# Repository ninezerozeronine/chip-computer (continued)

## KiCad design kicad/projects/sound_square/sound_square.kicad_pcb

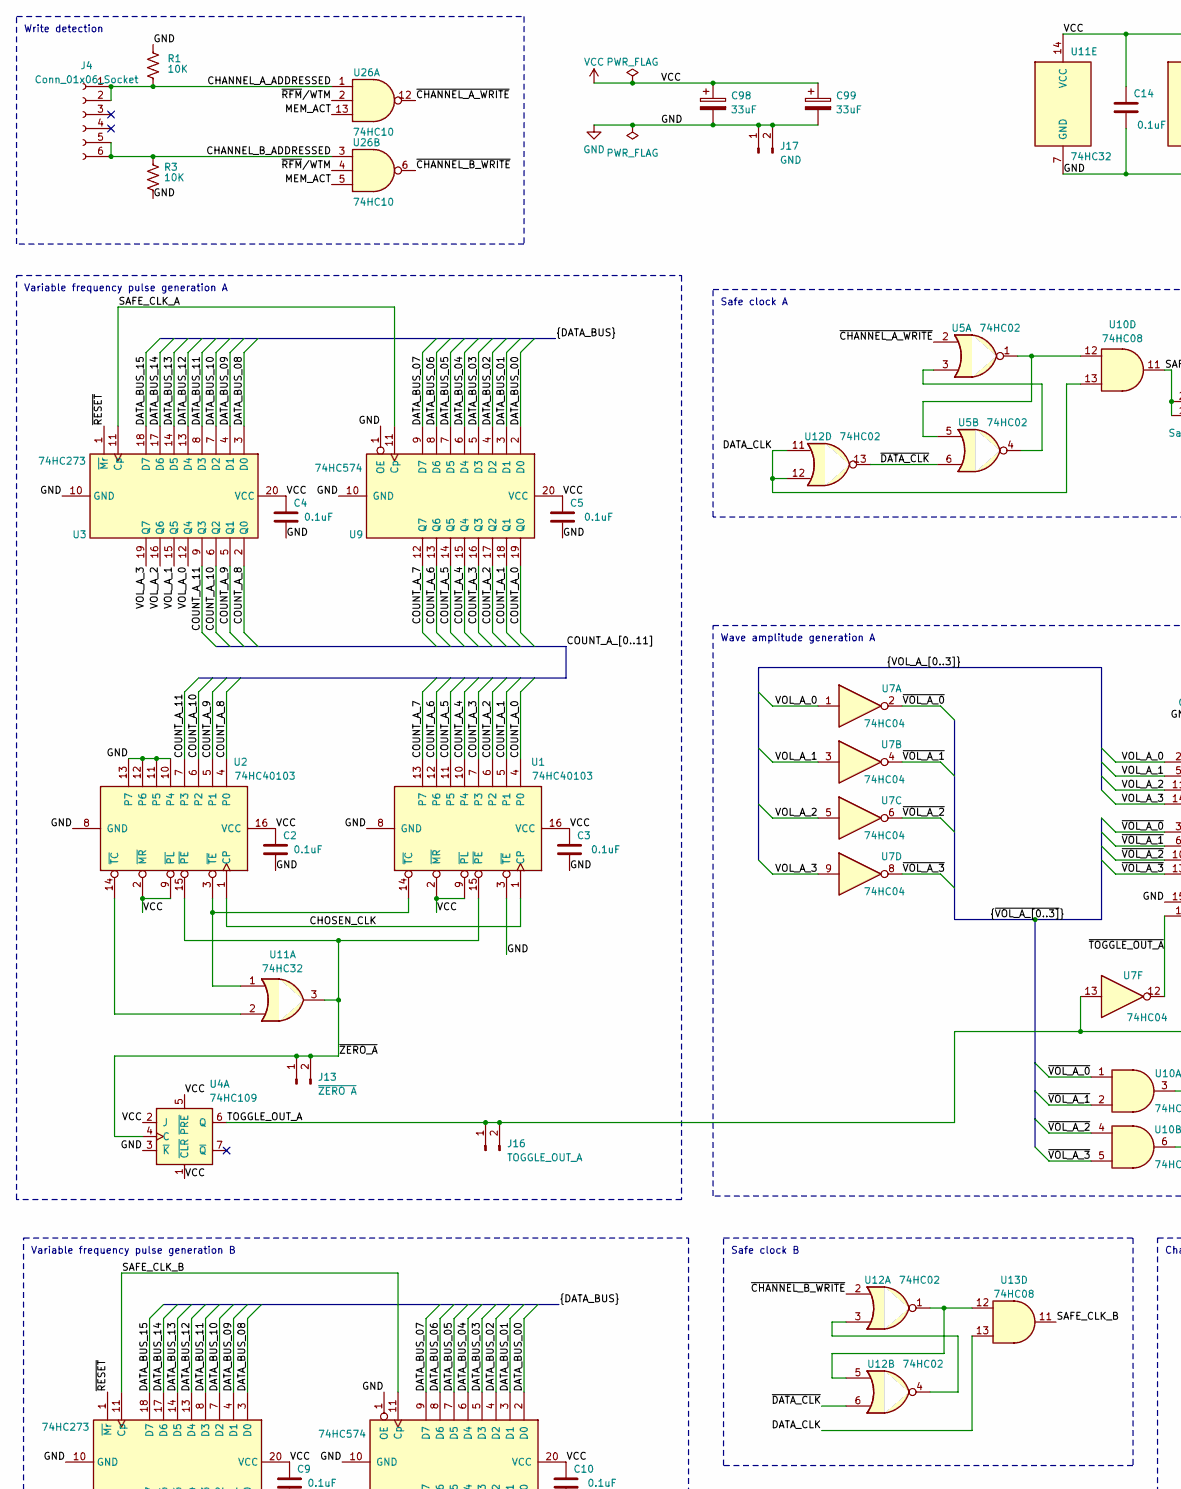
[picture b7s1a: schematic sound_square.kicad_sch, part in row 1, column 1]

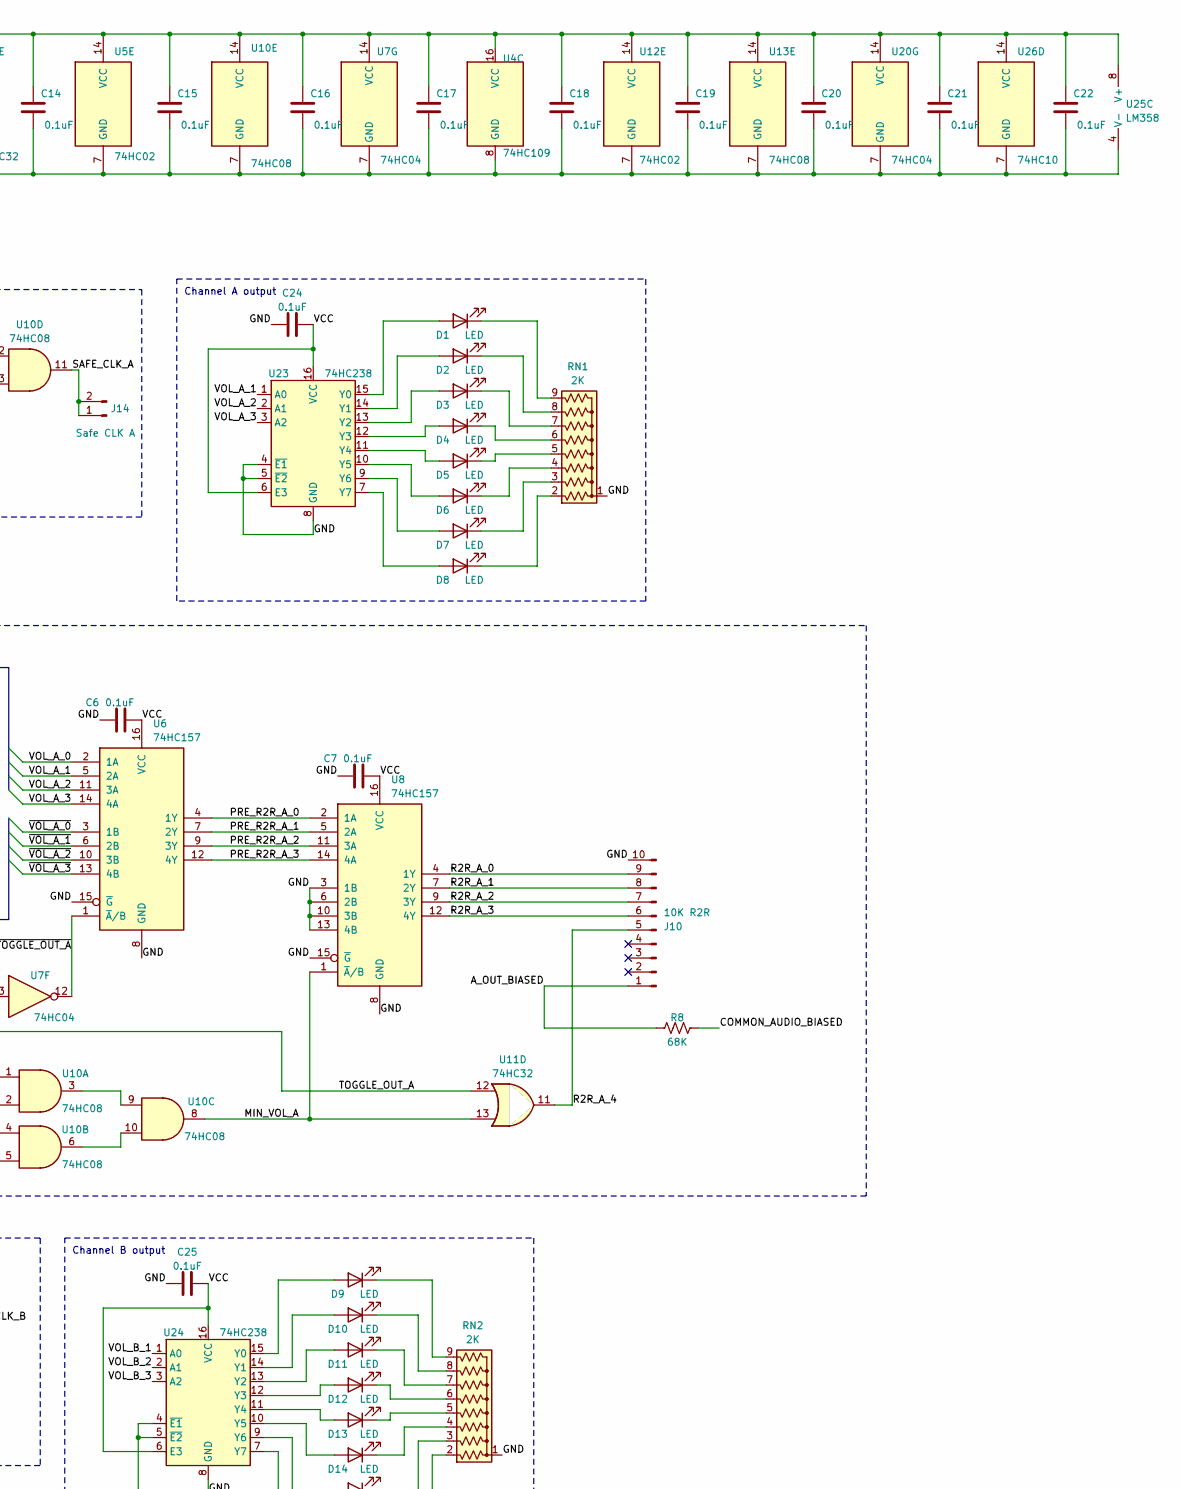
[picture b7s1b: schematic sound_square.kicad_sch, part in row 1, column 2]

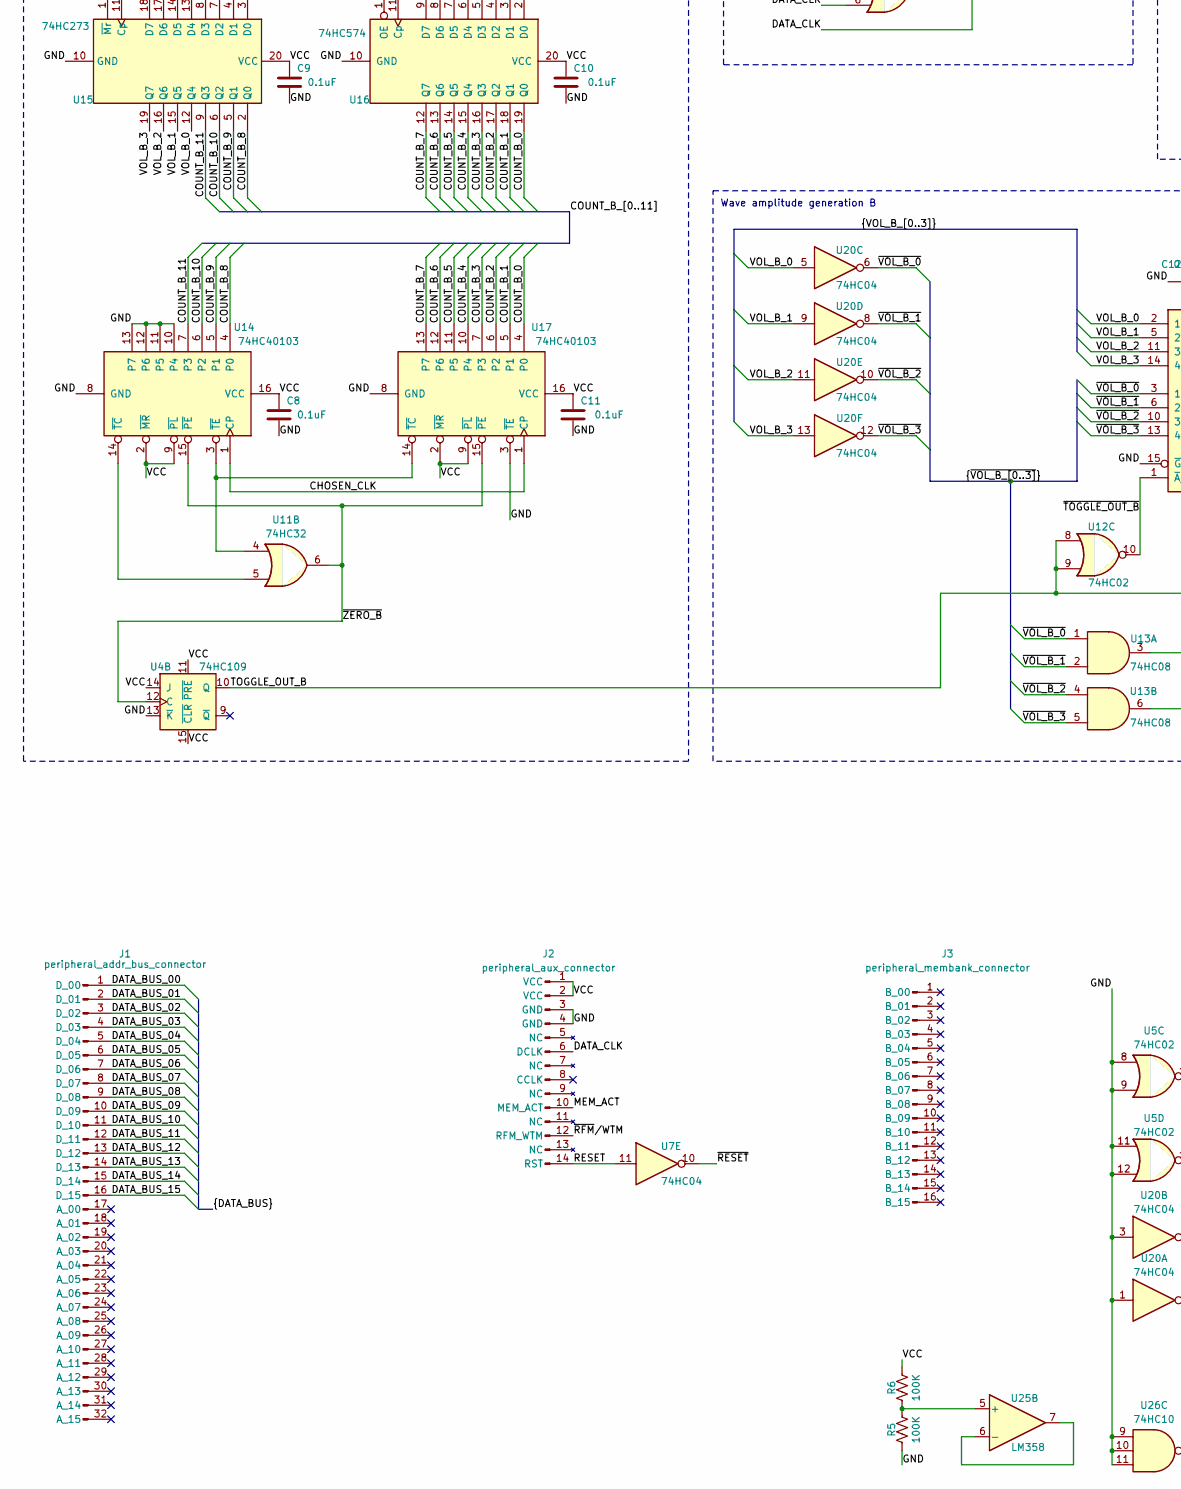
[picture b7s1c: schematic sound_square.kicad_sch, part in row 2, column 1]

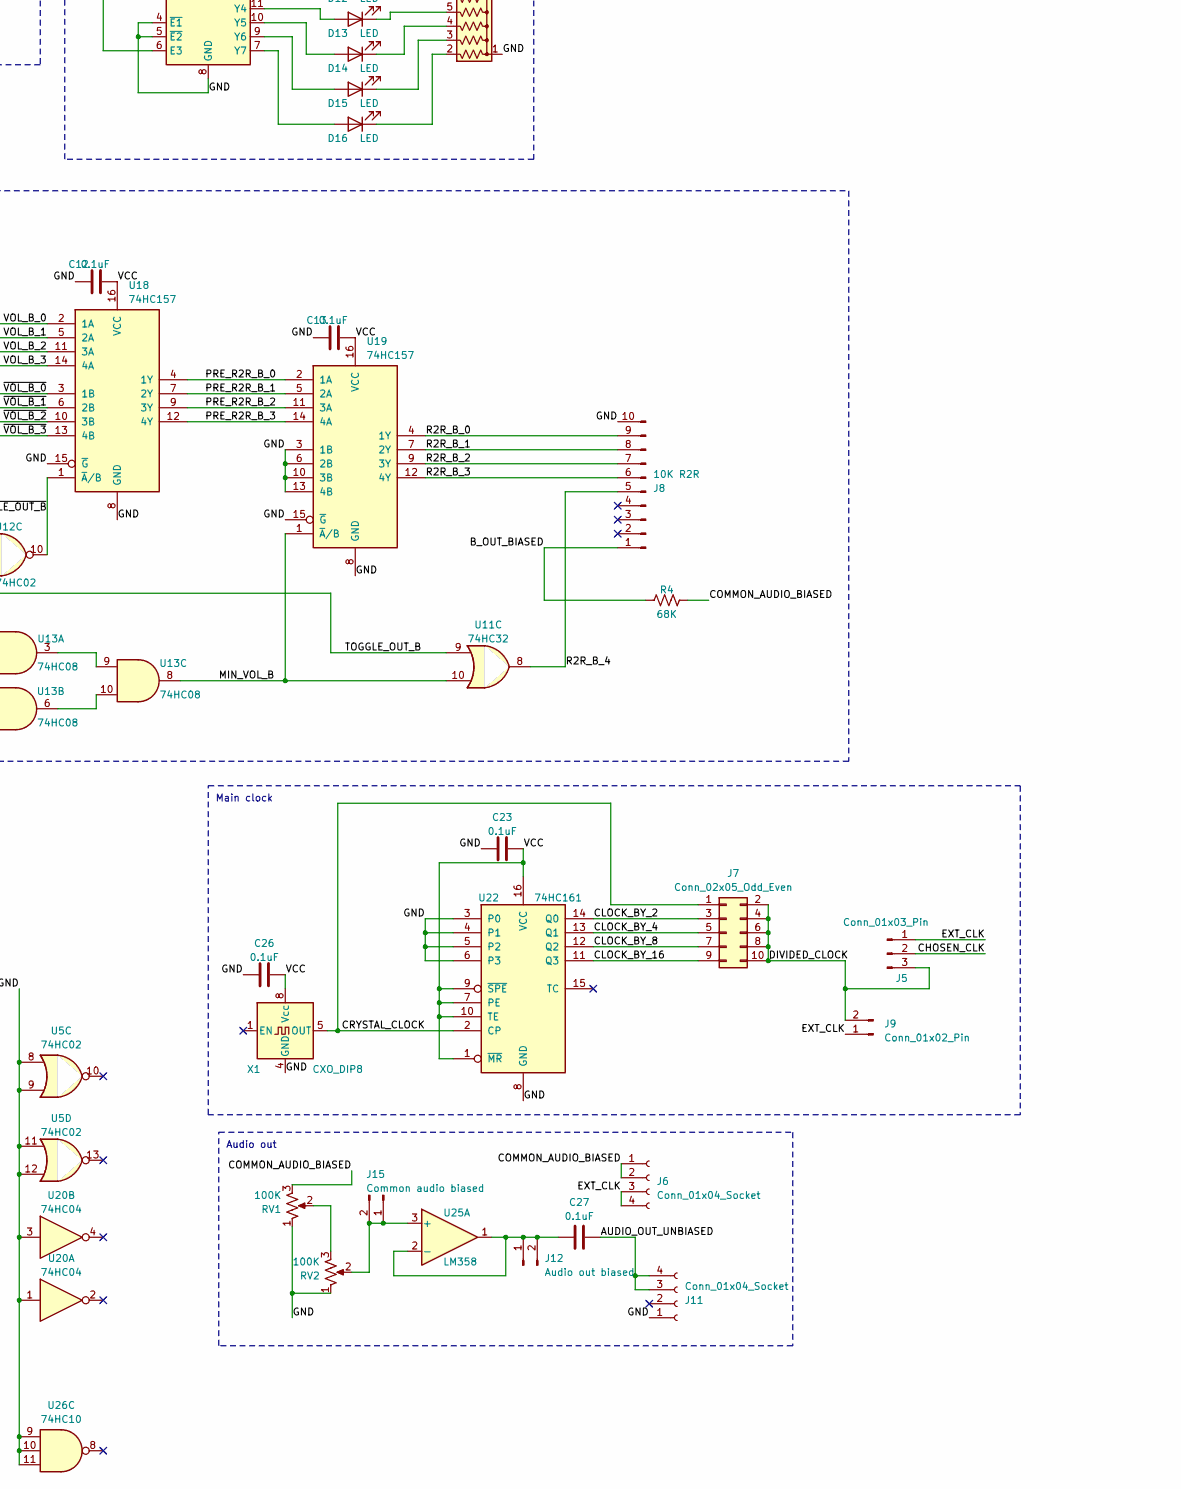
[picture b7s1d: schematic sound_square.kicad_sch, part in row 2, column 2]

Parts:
C2, C3, C4, C5, C6, C7, C8, C9, C10, C11, C12, C13, C14, C15, C16, C17, C18, C19, C20, C21, C22, C23, C24, C25, C26, C27: 0.1uF; C_Disc_D5.0mm_W2.5mm_P5.00mm
C98, C99: 33uF; CP_Radial_D6.3mm_P2.50mm
D1, D2, D3, D4, D5, D6, D7, D8, D9, D10, D11, D12, D13, D14, D15, D16: LED; LED_D5.0mm_Horizontal_O3.81mm_Z3.0mm
J1: peripheral_addr_bus_connector; peripheral-backplane-data-addr-anno
J2: peripheral_aux_connector; peripheral-backplane-aux
J3: peripheral_membank_connector; peripheral-backplane-membank
J4: Conn_01x06_Socket; PinSocket_1x06_P2.54mm_Horizontal
J5: Conn_01x03_Pin; PinHeader_1x03_P2.54mm_Vertical
J6, J11: Conn_01x04_Socket; PinSocket_1x04_P2.54mm_Horizontal
J7: Conn_02x05_Odd_Even; PinHeader_2x05_P2.54mm_Vertical
J8, J10: 10K R2R; R_Array_SIP10
J9: Conn_01x02_Pin; PinHeader_1x02_P2.54mm_Vertical
J12: Audio out biased; PinHeader_1x02_P2.54mm_Vertical
J13: ~{ZERO A}; PinHeader_1x02_P2.54mm_Vertical
J14: Safe CLK A; PinHeader_1x02_P2.54mm_Vertical
J15: Common audio biased; PinHeader_1x02_P2.54mm_Vertical
J16: TOGGLE_OUT_A; PinHeader_1x02_P2.54mm_Vertical
J17: GND; PinHeader_1x02_P2.54mm_Vertical
R1, R3: 10K; R_Axial_DIN0207_L6.3mm_D2.5mm_P10.16mm_Horizontal
R4, R8: 68K; R_Axial_DIN0207_L6.3mm_D2.5mm_P10.16mm_Horizontal
R5, R6: 100K; R_Axial_DIN0207_L6.3mm_D2.5mm_P10.16mm_Horizontal
RN1, RN2: 2K; R_Array_SIP9
RV1, RV2: 100K; Potentiometer_Bourns_3386P_Vertical
U1, U2, U14, U17: 74HC40103; DIP-16_W7.62mm_Socket
U3, U15: 74HC273; DIP-20_W7.62mm_Socket
U4: 74HC109; DIP-16_W7.62mm_Socket
U5, U12: 74HC02; DIP-14_W7.62mm_Socket
U6, U8, U18, U19: 74HC157; DIP-16_W7.62mm_Socket
U7, U20: 74HC04; DIP-14_W7.62mm_Socket
U9, U16: 74HC574; DIP-20_W7.62mm_Socket
U10, U13: 74HC08; DIP-14_W7.62mm_Socket
U11: 74HC32; DIP-14_W7.62mm_Socket
U22: 74HC161; DIP-16_W7.62mm_Socket
U23, U24: 74HC238; DIP-16_W7.62mm_Socket
U25: LM358; DIP-8_W7.62mm_Socket
U26: 74HC10; DIP-14_W7.62mm_Socket
X1: CXO_DIP8; Oscillator_DIP-8

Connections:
/AUDIO_OUT_UNBIASED: C27.2, J11.3, J11.4
/A_OUT_BIASED: J10.1, R8.1
/B_OUT_BIASED: J8.1, R4.1
/CHANNEL_A_ADDRESSED: J4.1, J4.2, R1.2, U26.1
/CHANNEL_B_ADDRESSED: J4.5, J4.6, R3.1, U26.3
/CHOSEN_CLK: J5.2, U1.1 (CP), U2.1 (CP), U14.1 (CP), U17.1 (CP)
/CLOCK_BY_2: J7.3, U22.14 (Q0)
/CLOCK_BY_4: J7.5, U22.13 (Q1)
/CLOCK_BY_8: J7.7, U22.12 (Q2)
/CLOCK_BY_16: J7.9, U22.11 (Q3)
/COMMON_AUDIO_BIASED: J6.1, J6.2, R4.2, R8.2, RV1.3
/COUNT_A_0: U1.4 (P0), U9.19 (Q0)
/COUNT_A_1: U1.5 (P1), U9.18 (Q1)
/COUNT_A_2: U1.6 (P2), U9.17 (Q2)
/COUNT_A_3: U1.7 (P3), U9.16 (Q3)
/COUNT_A_4: U1.10 (P4), U9.15 (Q4)
/COUNT_A_5: U1.11 (P5), U9.14 (Q5)
/COUNT_A_6: U1.12 (P6), U9.13 (Q6)
/COUNT_A_7: U1.13 (P7), U9.12 (Q7)
/COUNT_A_8: U2.4 (P0), U3.2 (Q0)
/COUNT_A_9: U2.5 (P1), U3.5 (Q1)
/COUNT_A_10: U2.6 (P2), U3.6 (Q2)
/COUNT_A_11: U2.7 (P3), U3.9 (Q3)
/COUNT_B_0: U16.19 (Q0), U17.4 (P0)
/COUNT_B_1: U16.18 (Q1), U17.5 (P1)
/COUNT_B_2: U16.17 (Q2), U17.6 (P2)
/COUNT_B_3: U16.16 (Q3), U17.7 (P3)
/COUNT_B_4: U16.15 (Q4), U17.10 (P4)
/COUNT_B_5: U16.14 (Q5), U17.11 (P5)
/COUNT_B_6: U16.13 (Q6), U17.12 (P6)
/COUNT_B_7: U16.12 (Q7), U17.13 (P7)
/COUNT_B_8: U14.4 (P0), U15.2 (Q0)
/COUNT_B_9: U14.5 (P1), U15.5 (Q1)
/COUNT_B_10: U14.6 (P2), U15.6 (Q2)
/COUNT_B_11: U14.7 (P3), U15.9 (Q3)
/CRYSTAL_CLOCK: J7.1, U22.2 (CP), X1.5 (OUT)
/DATA_BUS_00: J1.1 (D_00), U9.2 (D0), U16.2 (D0)
/DATA_BUS_01: J1.2 (D_01), U9.3 (D1), U16.3 (D1)
/DATA_BUS_02: J1.3 (D_02), U9.4 (D2), U16.4 (D2)
/DATA_BUS_03: J1.4 (D_03), U9.5 (D3), U16.5 (D3)
/DATA_BUS_04: J1.5 (D_04), U9.6 (D4), U16.6 (D4)
/DATA_BUS_05: J1.6 (D_05), U9.7 (D5), U16.7 (D5)
/DATA_BUS_06: J1.7 (D_06), U9.8 (D6), U16.8 (D6)
/DATA_BUS_07: J1.8 (D_07), U9.9 (D7), U16.9 (D7)
/DATA_BUS_08: J1.9 (D_08), U3.3 (D0), U15.3 (D0)
/DATA_BUS_09: J1.10 (D_09), U3.4 (D1), U15.4 (D1)
/DATA_BUS_10: J1.11 (D_10), U3.7 (D2), U15.7 (D2)
/DATA_BUS_11: J1.12 (D_11), U3.8 (D3), U15.8 (D3)
/DATA_BUS_12: J1.13 (D_12), U3.13 (D4), U15.13 (D4)
/DATA_BUS_13: J1.14 (D_13), U3.14 (D5), U15.14 (D5)
/DATA_BUS_14: J1.15 (D_14), U3.17 (D6), U15.17 (D6)
/DATA_BUS_15: J1.16 (D_15), U3.18 (D7), U15.18 (D7)
/DATA_CLK: J2.6 (DCLK), U10.13, U12.11, U12.12, U13.13
/DIVIDED_CLOCK: J5.3, J7.2, J7.4, J7.6, J7.8, J7.10, J9.2
/EXT_CLK: J5.1, J6.3, J6.4, J9.1
/MEM_ACT: J2.10 (MEM_ACT), U26.5, U26.13
/MIN_VOL_A: U8.1 (~A/B), U10.8, U11.13
/MIN_VOL_B: U11.10, U13.8, U19.1 (~A/B)
/PRE_R2R_A_0: U6.4 (1Y), U8.2 (1A)
/PRE_R2R_A_1: U6.7 (2Y), U8.5 (2A)
/PRE_R2R_A_2: U6.9 (3Y), U8.11 (3A)
/PRE_R2R_A_3: U6.12 (4Y), U8.14 (4A)
/PRE_R2R_B_0: U18.4 (1Y), U19.2 (1A)
/PRE_R2R_B_1: U18.7 (2Y), U19.5 (2A)
/PRE_R2R_B_2: U18.9 (3Y), U19.11 (3A)
/PRE_R2R_B_3: U18.12 (4Y), U19.14 (4A)
/R2R_A_0: J10.9, U8.4 (1Y)
/R2R_A_1: J10.8, U8.7 (2Y)
/R2R_A_2: J10.7, U8.9 (3Y)
/R2R_A_3: J10.6, U8.12 (4Y)
/R2R_A_4: J10.5, U11.11
/R2R_B_0: J8.9, U19.4 (1Y)
/R2R_B_1: J8.8, U19.7 (2Y)
/R2R_B_2: J8.7, U19.9 (3Y)
/R2R_B_3: J8.6, U19.12 (4Y)
/R2R_B_4: J8.5, U11.8
/RESET: J2.14 (RST), U7.11
/SAFE_CLK_A: J14.1, J14.2, U3.11 (Cp), U9.11 (Cp), U10.11
/SAFE_CLK_B: U13.11, U15.11 (Cp), U16.11 (Cp)
/TOGGLE_OUT_A: J16.1, J16.2, U4.6 (Q), U7.13, U11.12
/TOGGLE_OUT_B: U4.10 (Q), U11.9, U12.8, U12.9
/VOL_A_0: U3.12 (Q4), U6.2 (1A), U7.1
/VOL_A_1: U3.15 (Q5), U6.5 (2A), U7.3, U23.1 (A0)
/VOL_A_2: U3.16 (Q6), U6.11 (3A), U7.5, U23.2 (A1)
/VOL_A_3: U3.19 (Q7), U6.14 (4A), U7.9, U23.3 (A2)
/VOL_B_0: U15.12 (Q4), U18.2 (1A), U20.5
/VOL_B_1: U15.15 (Q5), U18.5 (2A), U20.9, U24.1 (A0)
/VOL_B_2: U15.16 (Q6), U18.11 (3A), U20.11, U24.2 (A1)
/VOL_B_3: U15.19 (Q7), U18.14 (4A), U20.13, U24.3 (A2)
/~CHANNEL_A_WRITE: U5.2, U26.12
/~CHANNEL_B_WRITE: U12.2, U26.6
/~DATA_CLK: U5.6, U12.6, U12.13
/~RESET: U3.1 (~Mr), U7.10, U15.1 (~Mr)
/~RFM/WTM: J2.12 (RFM_WTM), U26.2, U26.4
/~TOGGLE_OUT_A: U6.1 (~A/B), U7.12
/~TOGGLE_OUT_B: U12.10, U18.1 (~A/B)
/~VOL_A_0: U6.3 (1B), U7.2, U10.1
/~VOL_A_1: U6.6 (2B), U7.4, U10.2
/~VOL_A_2: U6.10 (3B), U7.6, U10.4
/~VOL_A_3: U6.13 (4B), U7.8, U10.5
/~VOL_B_0: U13.1, U18.3 (1B), U20.6
/~VOL_B_1: U13.2, U18.6 (2B), U20.8
/~VOL_B_2: U13.4, U18.10 (3B), U20.10
/~VOL_B_3: U13.5, U18.13 (4B), U20.12
/~ZERO_A: J13.1, J13.2, U1.15 (~PE), U2.15 (~PE), U4.4 (C), U11.3
/~ZERO_B: U4.12 (C), U11.6, U14.15 (~PE), U17.15 (~PE)
GND: C2.2, C3.2, C4.2, C5.2, C6.1, C7.1, C8.2, C9.2, C10.2, C11.2, C12.1, C13.1, C14.2, C15.2, C16.2, C17.2, C18.2, C19.2, C20.2, C21.2, C22.2, C23.1, C24.1, C25.1, C26.1, C98.2, C99.2, J2.3 (GND), J2.4 (GND), J8.10, J10.10, J11.1, J17.1, J17.2, R1.1, R3.2, R5.1, RN1.1 (common), RN2.1 (common), RV1.1, RV2.1, U1.3 (~TE), U1.8 (GND), U2.8 (GND), U2.10 (P4), U2.11 (P5), U2.12 (P6), U2.13 (P7), U3.10 (GND), U4.3 (~K), U4.8 (GND), U4.13 (~K), U5.7 (GND), U5.8, U5.9, U5.11, U5.12, U6.8 (GND), U6.15 (~G), U7.7 (GND), U8.3 (1B), U8.6 (2B), U8.8 (GND), U8.10 (3B), U8.13 (4B), U8.15 (~G), U9.1 (OE), U9.10 (GND), U10.7 (GND), U11.7 (GND), U12.7 (GND), U13.7 (GND), U14.8 (GND), U14.10 (P4), U14.11 (P5), U14.12 (P6), U14.13 (P7), U15.10 (GND), U16.1 (OE), U16.10 (GND), U17.3 (~TE), U17.8 (GND), U18.8 (GND), U18.15 (~G), U19.3 (1B), U19.6 (2B), U19.8 (GND), U19.10 (3B), U19.13 (4B), U19.15 (~G), U20.1, U20.3, U20.7 (GND), U22.3 (P0), U22.4 (P1), U22.5 (P2), U22.6 (P3), U22.8 (GND), U23.4 (~E1), U23.5 (~E2), U23.8 (GND), U24.4 (~E1), U24.5 (~E2), U24.8 (GND), U25.4 (V-), U26.7 (GND), U26.9, U26.10, U26.11, X1.4 (GND)
unnamed: D1.2 (A), U23.15 (Y0)
unnamed: D1.1 (K), RN1.9 (R8)
unnamed: D2.2 (A), U23.14 (Y1)
unnamed: D2.1 (K), RN1.8 (R7)
unnamed: D3.2 (A), U23.13 (Y2)
unnamed: D3.1 (K), RN1.7 (R6)
unnamed: D4.2 (A), U23.12 (Y3)
unnamed: D4.1 (K), RN1.6 (R5)
unnamed: D5.2 (A), U23.11 (Y4)
unnamed: D5.1 (K), RN1.5 (R4)
unnamed: D6.2 (A), U23.10 (Y5)
unnamed: D6.1 (K), RN1.4 (R3)
unnamed: D7.2 (A), U23.9 (Y6)
unnamed: D7.1 (K), RN1.3 (R2)
unnamed: D8.2 (A), U23.7 (Y7)
unnamed: D8.1 (K), RN1.2 (R1)
unnamed: D9.2 (A), U24.15 (Y0)
unnamed: D9.1 (K), RN2.9 (R8)
unnamed: D10.2 (A), U24.14 (Y1)
unnamed: D10.1 (K), RN2.8 (R7)
unnamed: D11.2 (A), U24.13 (Y2)
unnamed: D11.1 (K), RN2.7 (R6)
unnamed: D12.2 (A), U24.12 (Y3)
unnamed: D12.1 (K), RN2.6 (R5)
unnamed: D13.2 (A), U24.11 (Y4)
unnamed: D13.1 (K), RN2.5 (R4)
unnamed: D14.2 (A), U24.10 (Y5)
unnamed: D14.1 (K), RN2.4 (R3)
unnamed: D15.2 (A), U24.9 (Y6)
unnamed: D15.1 (K), RN2.3 (R2)
unnamed: D16.2 (A), U24.7 (Y7)
unnamed: D16.1 (K), RN2.2 (R1)
unnamed: C27.1, J12.1, J12.2, U25.1, U25.2 (-)
unnamed: J15.1, J15.2, RV2.2, U25.3 (+)
unnamed: RV1.2, RV2.3
unnamed: U1.14 (~TC), U2.3 (~TE), U11.1
unnamed: U2.14 (~TC), U11.2
unnamed: U5.3, U5.4
unnamed: U10.3, U10.9
unnamed: U10.6, U10.10
unnamed: U5.1, U5.5, U10.12
unnamed: U12.1, U12.5, U13.12
unnamed: U12.3, U12.4
unnamed: U13.3, U13.9
unnamed: U13.6, U13.10
unnamed: U11.5, U14.14 (~TC)
unnamed: U11.4, U14.3 (~TE), U17.14 (~TC)
unnamed: R5.2, R6.1, U25.5 (+)
unnamed: U25.6 (-), U25.7
VCC: C2.1, C3.1, C4.1, C5.1, C6.2, C7.2, C8.1, C9.1, C10.1, C11.1, C12.2, C13.2, C14.1, C15.1, C16.1, C17.1, C18.1, C19.1, C20.1, C21.1, C22.1, C23.2, C24.2, C25.2, C26.2, C98.1, C99.1, J2.1 (VCC), J2.2 (VCC), R6.2, U1.2 (~MR), U1.9 (~PL), U1.16 (VCC), U2.2 (~MR), U2.9 (~PL), U2.16 (VCC), U3.20 (VCC), U4.1 (~CLR), U4.2 (J), U4.5 (~PRE), U4.11 (~PRE), U4.14 (J), U4.15 (~CLR), U4.16 (VCC), U5.14 (VCC), U6.16 (VCC), U7.14 (VCC), U8.16 (VCC), U9.20 (VCC), U10.14 (VCC), U11.14 (VCC), U12.14 (VCC), U13.14 (VCC), U14.2 (~MR), U14.9 (~PL), U14.16 (VCC), U15.20 (VCC), U16.20 (VCC), U17.2 (~MR), U17.9 (~PL), U17.16 (VCC), U18.16 (VCC), U19.16 (VCC), U20.14 (VCC), U22.1 (~MR), U22.7 (PE), U22.9 (~SPE), U22.10 (TE), U22.16 (VCC), U23.6 (E3), U23.16 (VCC), U24.6 (E3), U24.16 (VCC), U25.8 (V+), U26.14 (VCC), X1.8 (Vcc)

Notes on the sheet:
Channel B output
Write detection
Channel A output
Wave amplitude generation A
Safe clock A
Safe clock B
Wave amplitude generation B
Variable frequency pulse generation A
Main clock
Audio out
Variable frequency pulse generation B

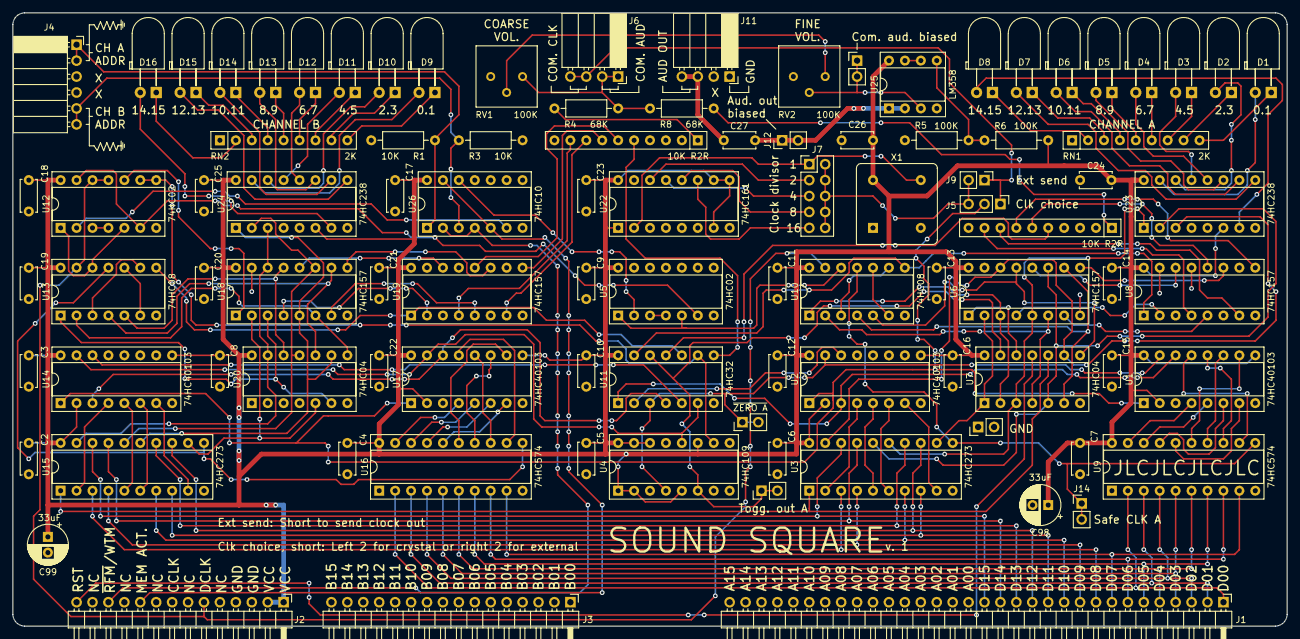
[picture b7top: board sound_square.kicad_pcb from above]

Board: 2 copper layers, 203.2 x 97.8 mm, 97 parts (0 on the bottom side), 157 nets.

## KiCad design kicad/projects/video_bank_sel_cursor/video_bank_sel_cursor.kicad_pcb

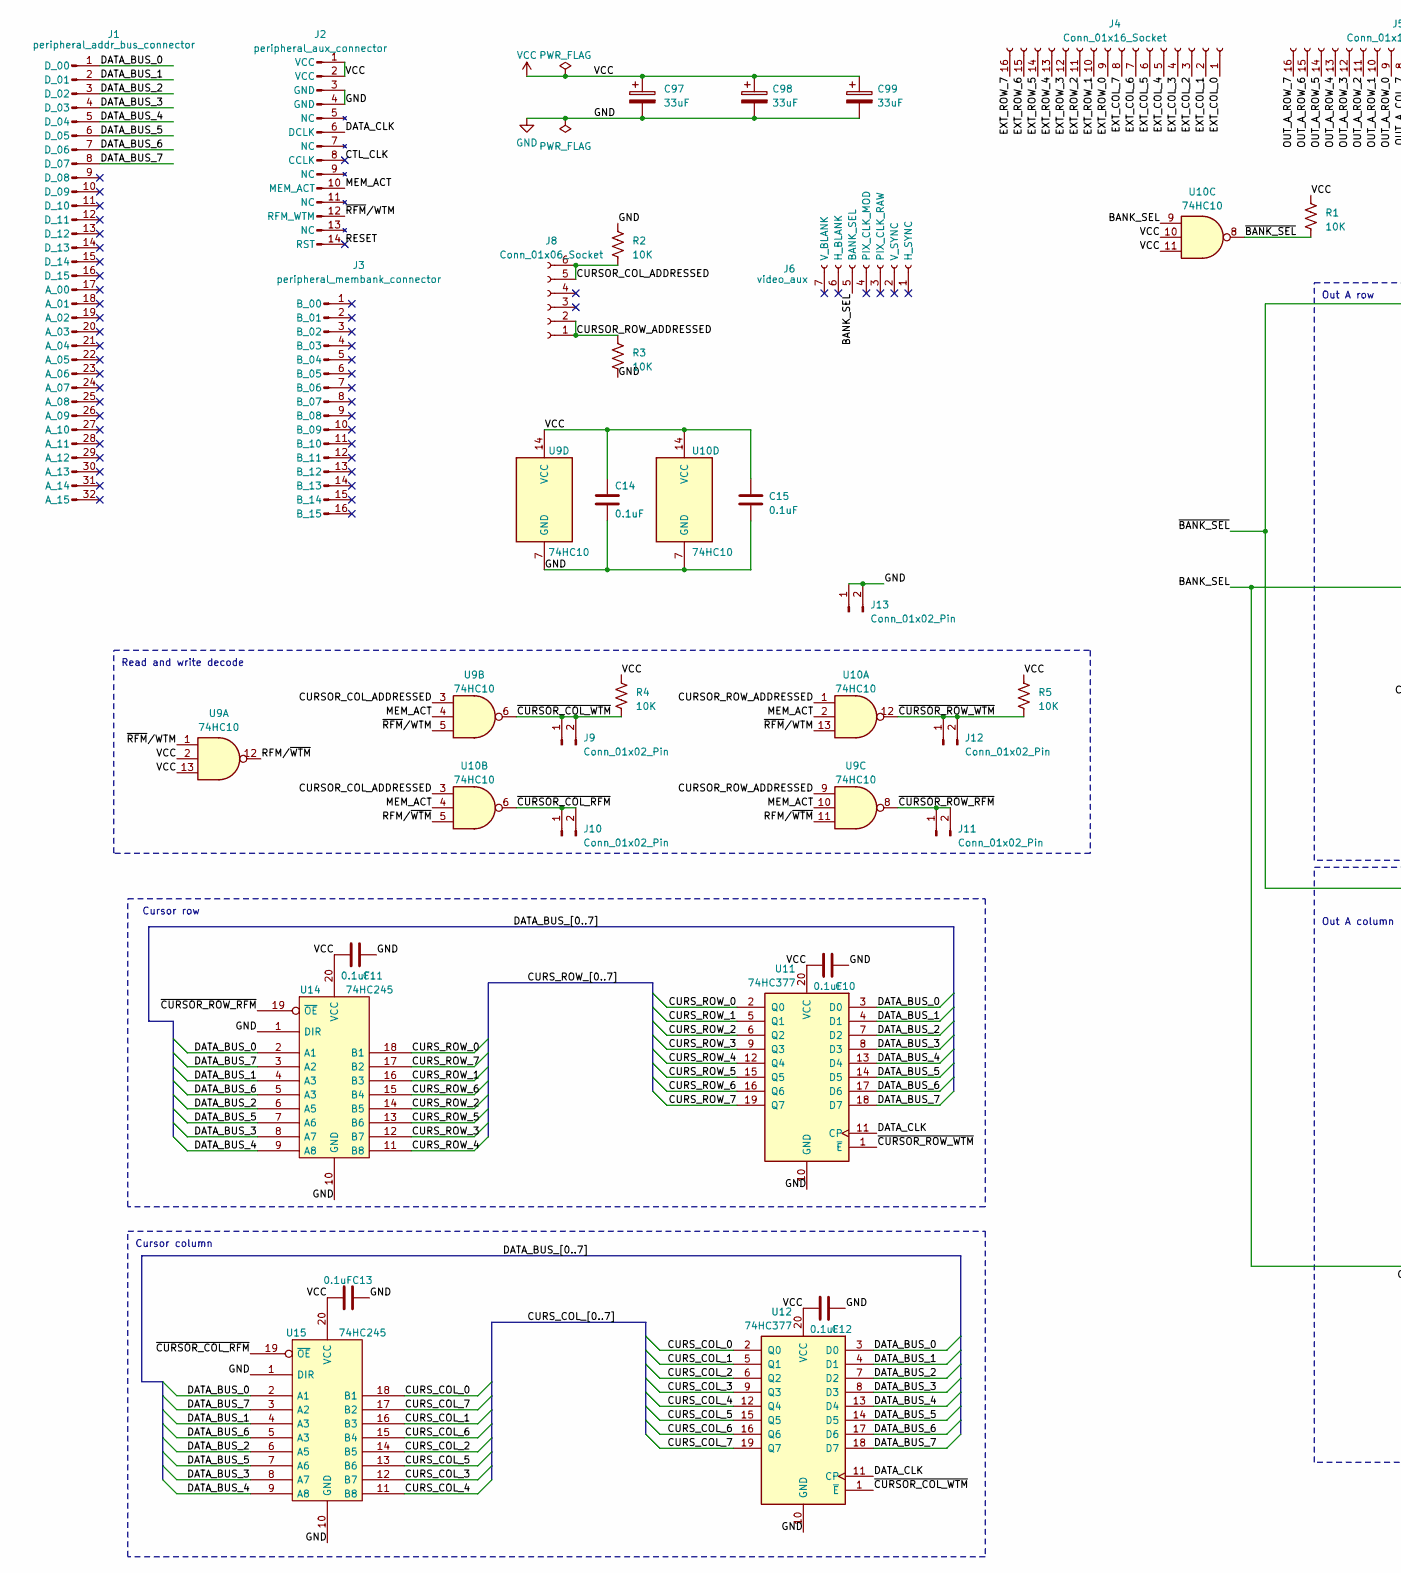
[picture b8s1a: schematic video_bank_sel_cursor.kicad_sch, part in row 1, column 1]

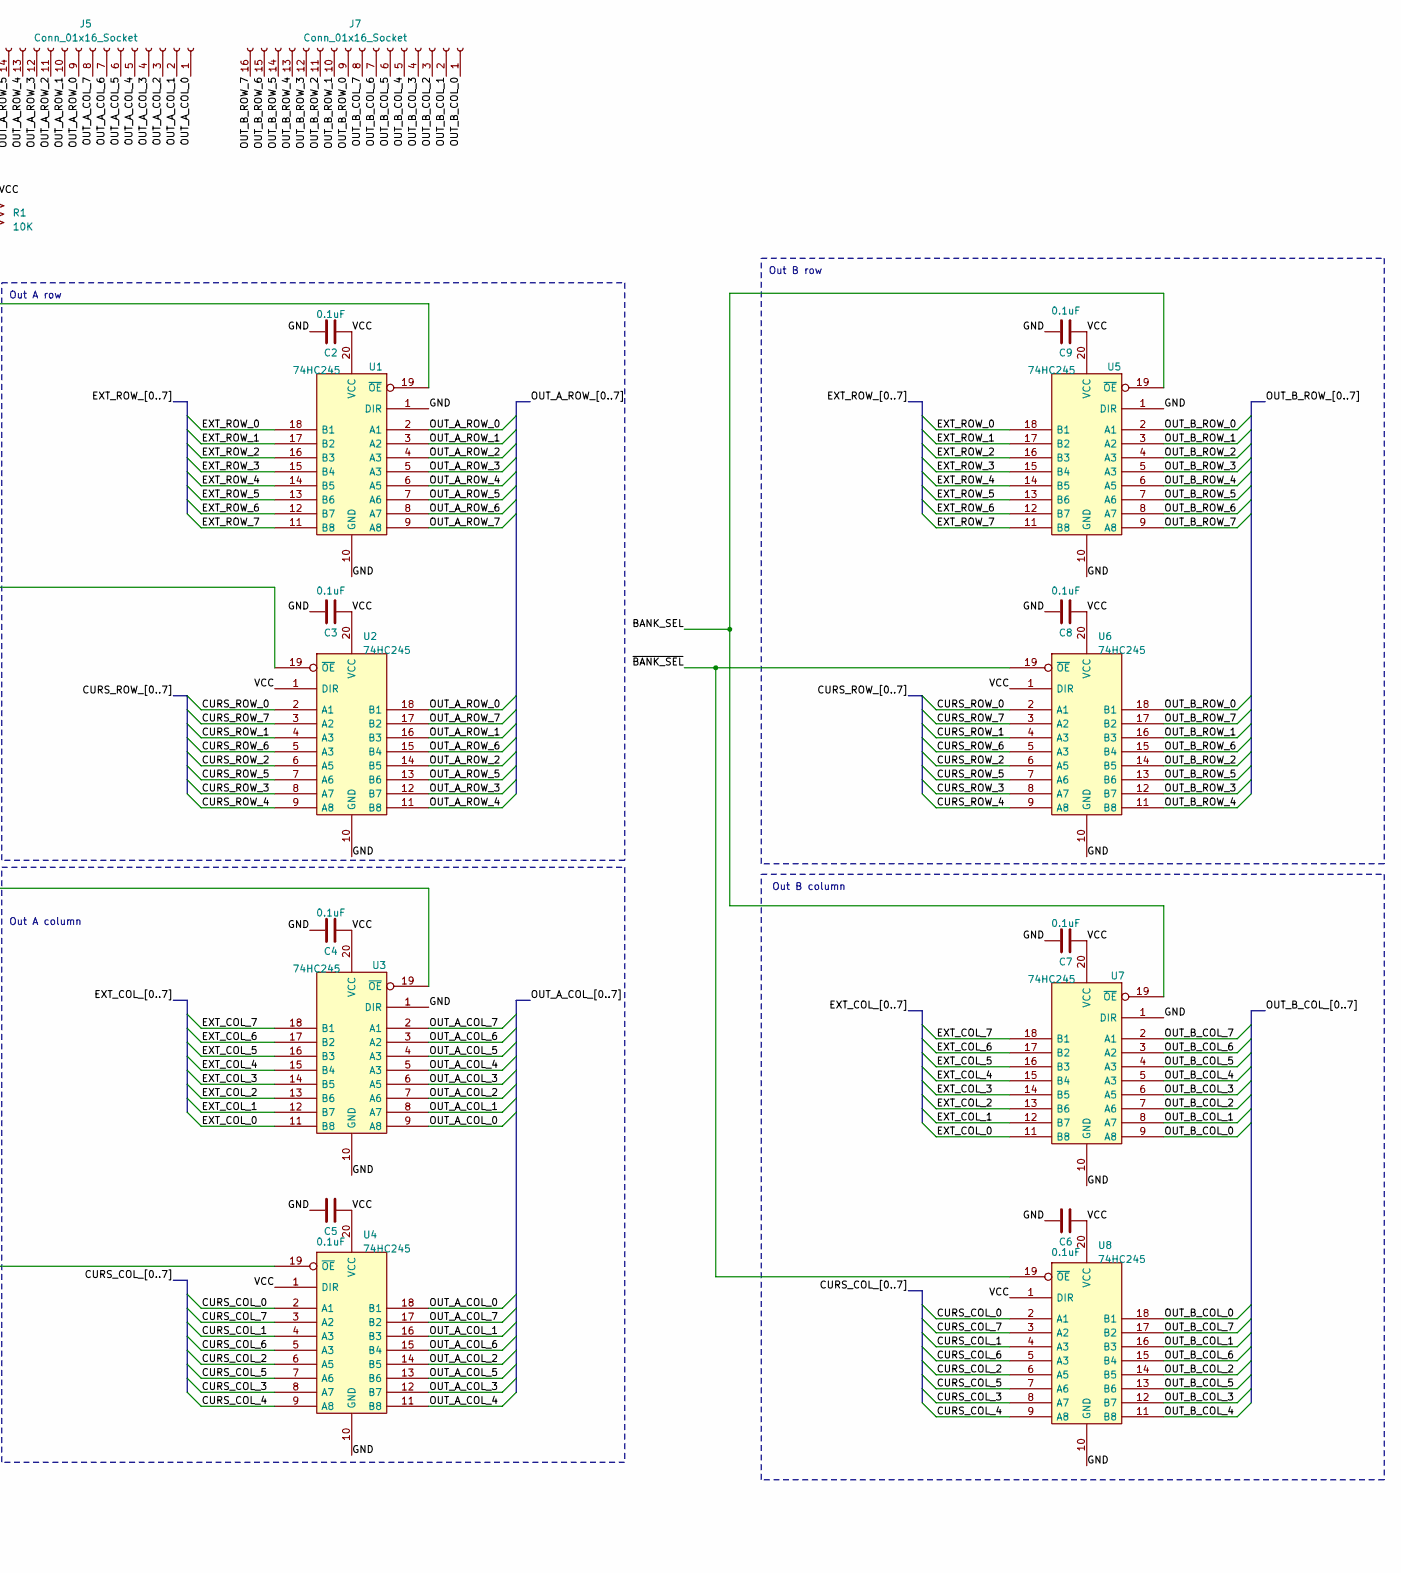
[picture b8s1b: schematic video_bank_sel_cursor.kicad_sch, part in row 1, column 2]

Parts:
C2, C3, C4, C5, C6, C7, C8, C9, C10, C11, C12, C13, C14, C15: 0.1uF; C_Disc_D5.0mm_W2.5mm_P5.00mm
C97, C98, C99: 33uF; CP_Radial_D6.3mm_P2.50mm
J1: peripheral_addr_bus_connector; peripheral-backplane-data-addr-anno
J2: peripheral_aux_connector; peripheral-backplane-aux
J3: peripheral_membank_connector; peripheral-backplane-membank
J4, J5, J7: Conn_01x16_Socket; PinSocket_1x16_P2.54mm_Horizontal
J6: video_aux; PinSocket_1x07_P2.54mm_Horizontal
J8: Conn_01x06_Socket; PinSocket_1x06_P2.54mm_Horizontal
J9, J10, J11, J12, J13: Conn_01x02_Pin; PinHeader_1x02_P2.54mm_Vertical
R1, R2, R3, R4, R5: 10K; R_Axial_DIN0207_L6.3mm_D2.5mm_P10.16mm_Horizontal
U1, U2, U3, U4, U5, U6, U7, U8, U14, U15: 74HC245; DIP-20_W7.62mm_Socket
U9, U10: 74HC10; DIP-14_W7.62mm_Socket
U11, U12: 74HC377; DIP-20_W7.62mm_Socket

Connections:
/BANK_SEL: J6.5 (BANK_SEL), U2.19 (~OE), U4.19 (~OE), U5.19 (~OE), U7.19 (~OE), U10.9
/CTL_CLK: J2.8 (CCLK)
/CURSOR_COL_ADDRESSED: J8.5, J8.6, R2.2, U9.3, U10.3
/CURSOR_ROW_ADDRESSED: J8.1, J8.2, R3.1, U9.9, U10.1
/CURS_COL_0: U4.2 (A1), U8.2 (A1), U12.2 (Q0), U15.18 (B1)
/CURS_COL_1: U4.4 (A3), U8.4 (A3), U12.5 (Q1), U15.16 (B3)
/CURS_COL_2: U4.6 (A5), U8.6 (A5), U12.6 (Q2), U15.14 (B5)
/CURS_COL_3: U4.8 (A7), U8.8 (A7), U12.9 (Q3), U15.12 (B7)
/CURS_COL_4: U4.9 (A8), U8.9 (A8), U12.12 (Q4), U15.11 (B8)
/CURS_COL_5: U4.7 (A6), U8.7 (A6), U12.15 (Q5), U15.13 (B6)
/CURS_COL_6: U4.5 (A3), U8.5 (A3), U12.16 (Q6), U15.15 (B4)
/CURS_COL_7: U4.3 (A2), U8.3 (A2), U12.19 (Q7), U15.17 (B2)
/CURS_ROW_0: U2.2 (A1), U6.2 (A1), U11.2 (Q0), U14.18 (B1)
/CURS_ROW_1: U2.4 (A3), U6.4 (A3), U11.5 (Q1), U14.16 (B3)
/CURS_ROW_2: U2.6 (A5), U6.6 (A5), U11.6 (Q2), U14.14 (B5)
/CURS_ROW_3: U2.8 (A7), U6.8 (A7), U11.9 (Q3), U14.12 (B7)
/CURS_ROW_4: U2.9 (A8), U6.9 (A8), U11.12 (Q4), U14.11 (B8)
/CURS_ROW_5: U2.7 (A6), U6.7 (A6), U11.15 (Q5), U14.13 (B6)
/CURS_ROW_6: U2.5 (A3), U6.5 (A3), U11.16 (Q6), U14.15 (B4)
/CURS_ROW_7: U2.3 (A2), U6.3 (A2), U11.19 (Q7), U14.17 (B2)
/DATA_BUS_0: J1.1 (D_00), U11.3 (D0), U12.3 (D0), U14.2 (A1), U15.2 (A1)
/DATA_BUS_1: J1.2 (D_01), U11.4 (D1), U12.4 (D1), U14.4 (A3), U15.4 (A3)
/DATA_BUS_2: J1.3 (D_02), U11.7 (D2), U12.7 (D2), U14.6 (A5), U15.6 (A5)
/DATA_BUS_3: J1.4 (D_03), U11.8 (D3), U12.8 (D3), U14.8 (A7), U15.8 (A7)
/DATA_BUS_4: J1.5 (D_04), U11.13 (D4), U12.13 (D4), U14.9 (A8), U15.9 (A8)
/DATA_BUS_5: J1.6 (D_05), U11.14 (D5), U12.14 (D5), U14.7 (A6), U15.7 (A6)
/DATA_BUS_6: J1.7 (D_06), U11.17 (D6), U12.17 (D6), U14.5 (A3), U15.5 (A3)
/DATA_BUS_7: J1.8 (D_07), U11.18 (D7), U12.18 (D7), U14.3 (A2), U15.3 (A2)
/DATA_CLK: J2.6 (DCLK), U11.11 (CP), U12.11 (CP)
/EXT_COL_0: J4.1, U3.11 (B8), U7.11 (B8)
/EXT_COL_1: J4.2, U3.12 (B7), U7.12 (B7)
/EXT_COL_2: J4.3, U3.13 (B6), U7.13 (B6)
/EXT_COL_3: J4.4, U3.14 (B5), U7.14 (B5)
/EXT_COL_4: J4.5, U3.15 (B4), U7.15 (B4)
/EXT_COL_5: J4.6, U3.16 (B3), U7.16 (B3)
/EXT_COL_6: J4.7, U3.17 (B2), U7.17 (B2)
/EXT_COL_7: J4.8, U3.18 (B1), U7.18 (B1)
/EXT_ROW_0: J4.9, U1.18 (B1), U5.18 (B1)
/EXT_ROW_1: J4.10, U1.17 (B2), U5.17 (B2)
/EXT_ROW_2: J4.11, U1.16 (B3), U5.16 (B3)
/EXT_ROW_3: J4.12, U1.15 (B4), U5.15 (B4)
/EXT_ROW_4: J4.13, U1.14 (B5), U5.14 (B5)
/EXT_ROW_5: J4.14, U1.13 (B6), U5.13 (B6)
/EXT_ROW_6: J4.15, U1.12 (B7), U5.12 (B7)
/EXT_ROW_7: J4.16, U1.11 (B8), U5.11 (B8)
/MEM_ACT: J2.10 (MEM_ACT), U9.4, U9.10, U10.2, U10.4
/OUT_A_COL_0: J5.1, U3.9 (A8), U4.18 (B1)
/OUT_A_COL_1: J5.2, U3.8 (A7), U4.16 (B3)
/OUT_A_COL_2: J5.3, U3.7 (A6), U4.14 (B5)
/OUT_A_COL_3: J5.4, U3.6 (A5), U4.12 (B7)
/OUT_A_COL_4: J5.5, U3.5 (A3), U4.11 (B8)
/OUT_A_COL_5: J5.6, U3.4 (A3), U4.13 (B6)
/OUT_A_COL_6: J5.7, U3.3 (A2), U4.15 (B4)
/OUT_A_COL_7: J5.8, U3.2 (A1), U4.17 (B2)
/OUT_A_ROW_0: J5.9, U1.2 (A1), U2.18 (B1)
/OUT_A_ROW_1: J5.10, U1.3 (A2), U2.16 (B3)
/OUT_A_ROW_2: J5.11, U1.4 (A3), U2.14 (B5)
/OUT_A_ROW_3: J5.12, U1.5 (A3), U2.12 (B7)
/OUT_A_ROW_4: J5.13, U1.6 (A5), U2.11 (B8)
/OUT_A_ROW_5: J5.14, U1.7 (A6), U2.13 (B6)
/OUT_A_ROW_6: J5.15, U1.8 (A7), U2.15 (B4)
/OUT_A_ROW_7: J5.16, U1.9 (A8), U2.17 (B2)
/OUT_B_COL_0: J7.1, U7.9 (A8), U8.18 (B1)
/OUT_B_COL_1: J7.2, U7.8 (A7), U8.16 (B3)
/OUT_B_COL_2: J7.3, U7.7 (A6), U8.14 (B5)
/OUT_B_COL_3: J7.4, U7.6 (A5), U8.12 (B7)
/OUT_B_COL_4: J7.5, U7.5 (A3), U8.11 (B8)
/OUT_B_COL_5: J7.6, U7.4 (A3), U8.13 (B6)
/OUT_B_COL_6: J7.7, U7.3 (A2), U8.15 (B4)
/OUT_B_COL_7: J7.8, U7.2 (A1), U8.17 (B2)
/OUT_B_ROW_0: J7.9, U5.2 (A1), U6.18 (B1)
/OUT_B_ROW_1: J7.10, U5.3 (A2), U6.16 (B3)
/OUT_B_ROW_2: J7.11, U5.4 (A3), U6.14 (B5)
/OUT_B_ROW_3: J7.12, U5.5 (A3), U6.12 (B7)
/OUT_B_ROW_4: J7.13, U5.6 (A5), U6.11 (B8)
/OUT_B_ROW_5: J7.14, U5.7 (A6), U6.13 (B6)
/OUT_B_ROW_6: J7.15, U5.8 (A7), U6.15 (B4)
/OUT_B_ROW_7: J7.16, U5.9 (A8), U6.17 (B2)
/RESET: J2.14 (RST)
/RFM/~WTM: U9.11, U9.12, U10.5
/~BANK_SEL: R1.1, U1.19 (~OE), U3.19 (~OE), U6.19 (~OE), U8.19 (~OE), U10.8
/~CURSOR_COL_RFM: J10.1, J10.2, U10.6, U15.19 (~OE)
/~CURSOR_COL_WTM: J9.1, J9.2, R4.1, U9.6, U12.1 (~E)
/~CURSOR_ROW_RFM: J11.1, J11.2, U9.8, U14.19 (~OE)
/~CURSOR_ROW_WTM: J12.1, J12.2, R5.1, U10.12, U11.1 (~E)
/~RFM/WTM: J2.12 (RFM_WTM), U9.1, U9.5, U10.13
GND: C2.1, C3.1, C4.1, C5.1, C6.1, C7.1, C8.1, C9.1, C10.1, C11.1, C12.1, C13.1, C14.2, C15.2, C97.2, C98.2, C99.2, J2.3 (GND), J2.4 (GND), J13.1, J13.2, R2.1, R3.2, U1.1 (DIR), U1.10 (GND), U2.10 (GND), U3.1 (DIR), U3.10 (GND), U4.10 (GND), U5.1 (DIR), U5.10 (GND), U6.10 (GND), U7.1 (DIR), U7.10 (GND), U8.10 (GND), U9.7 (GND), U10.7 (GND), U11.10 (GND), U12.10 (GND), U14.1 (DIR), U14.10 (GND), U15.1 (DIR), U15.10 (GND)
VCC: C2.2, C3.2, C4.2, C5.2, C6.2, C7.2, C8.2, C9.2, C10.2, C11.2, C12.2, C13.2, C14.1, C15.1, C97.1, C98.1, C99.1, J2.1 (VCC), J2.2 (VCC), R1.2, R4.2, R5.2, U1.20 (VCC), U2.1 (DIR), U2.20 (VCC), U3.20 (VCC), U4.1 (DIR), U4.20 (VCC), U5.20 (VCC), U6.1 (DIR), U6.20 (VCC), U7.20 (VCC), U8.1 (DIR), U8.20 (VCC), U9.2, U9.13, U9.14 (VCC), U10.10, U10.11, U10.14 (VCC), U11.20 (VCC), U12.20 (VCC), U14.20 (VCC), U15.20 (VCC)

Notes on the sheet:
Out B column
Out A column
Out B row
Cursor column
Out A row
Read and write decode
Cursor row

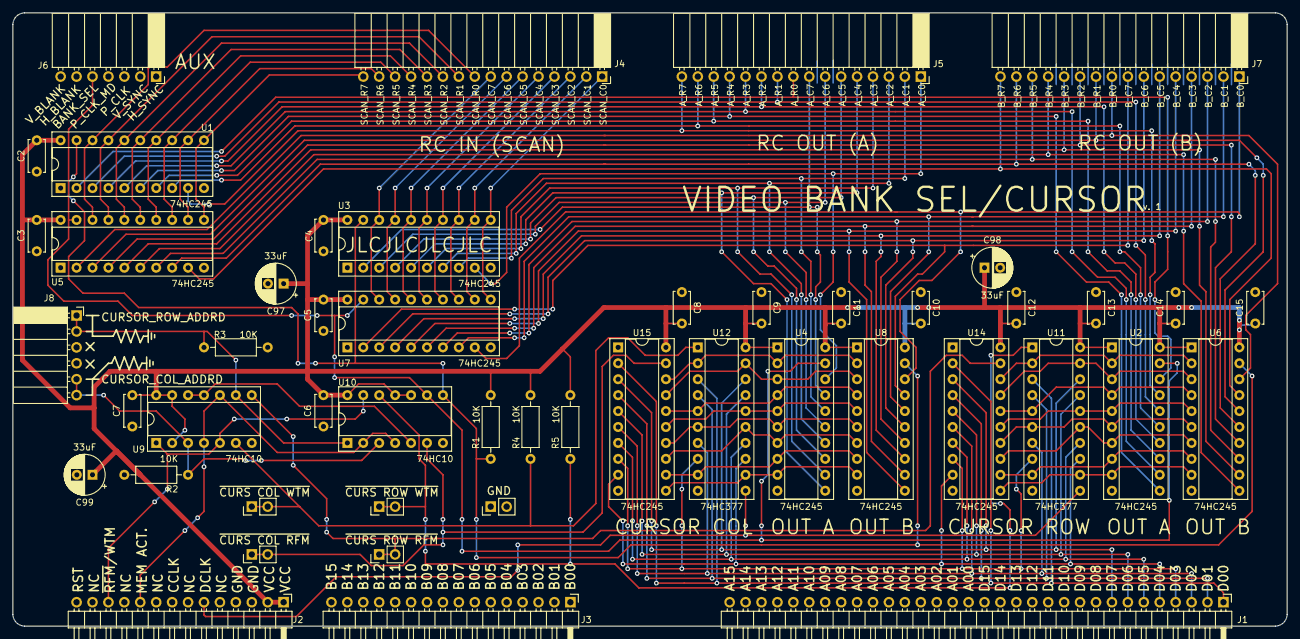
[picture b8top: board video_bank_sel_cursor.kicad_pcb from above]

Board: 2 copper layers, 203.2 x 97.8 mm, 49 parts (0 on the bottom side), 86 nets.
